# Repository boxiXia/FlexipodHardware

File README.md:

# FlexipodHardware

## 3D rendering and dimension of Flexipod

CAD model for the Flexipod

Flexipod stand on sand

## Prerequisite
Software: Inventor and Cura(or some other slice software for 3D printing)     
Filament: [Cheetah flexible filament, Ninjatek](https://ninjatek.com/cheetah/)
          [PolyMax™ PC, Playmaker](https://www.amazon.com/dp/B01KT3K0FW/?coliid=ISKG6U7RH7ZF8&colid=118CNRRRVL2LQ&psc=1&ref_=lv_ov_lig_dp_it)    
Super glue: [Gorilla Super Glue](https://www.amazon.com/Gorilla-Super-Brush-Nozzle-Applicator/dp/B01LYO4R4I/ref=sr_1_4?crid=1XCD6SS1SOGKY&dchild=1&keywords=super+glue&sprefix=super%2Caps%2C170&sr=8-4)

## Mechiancl parts

All the printed parts are printed by a FDM 3D printer(Troodon Core-XY printer, VIVEDINO) with a standard 0.4 mm nozzle at 0.2 mm layer height. For soft print, skins are only printed at mating surfaces, since the outer skins of the printed parts will greatly reduce the flexibility.

1. leg: print with 16% infill density(Gyroid pattern) and 80% flow using flexible TPU (Cheetah flexible filament, Ninjatek).

2. leg adaptor: rigid filament (PolyMax™ PC, Playmaker)

3. motor mount outer part: print with 20% infill density(Gyroid pattern) and 90% flow using flexible TPU (Cheetah flexible filament, Ninjatek).

4. [bearing: ](https://www.amazon.com/6806-Ceramic-Cartridge-Bearing-30x42x7mm/dp/B01MU6Z46A/ref=sr_1_3?dchild=1&keywords=6806-2RS&qid=1604034211&sr=8-3)

5. motor mount inner part: print with 20% infill density(Gyroid pattern) and 90% flow using flexible TPU (Cheetah flexible filament, Ninjatek).

6. motor shell: rigid filament (PolyMax™ PC, Playmaker)

7. body cover: print with 20% infill density(Gyroid pattern) and 90% flow using flexible TPU (Cheetah flexible filament, Ninjatek).

8. upper body: print with 20% infill density(Gyroid pattern) and 90% flow using flexible TPU (Cheetah flexible filament, Ninjatek).

9. lower body: print with 20% infill density(Gyroid pattern) and 90% flow using flexible TPU (Cheetah flexible filament, Ninjatek).

## Electrical parts
electrical system of the Flexipod  

1. [Raspberry Pi 4B](https://www.amazon.com/Raspberry-Model-2019-Quad-Bluetooth/dp/B07TC2BK1X/ref=sr_1_5?crid=2TAFP75A787CM&dchild=1&keywords=raspberry+pi+4&sprefix=raspberr%2Caps%2C187&sr=8-5)

2. [5V Voltage Regulator](https://www.pololu.com/product/4091)

3. [5S Battery](https://www.amazon.com/Ovonic-1300mAh-Battery-Professional-Competitions/dp/B07JXZCHWM/ref=sr_1_4?dchild=1&keywords=Ovonic+5S+battery&qid=1598477273&sr=8-4)

4. [CAN Transceivez](https://www.amazon.com/dp/B07V5LGBC8/?coliid=I3FNNXJG3YL6HU&colid=34AXXXH87PSUB&psc=1&ref_=lv_ov_lig_dp_it)

5. [Teensy 4.0](https://www.amazon.com/Teensy-4-0-With-Pins/dp/B08259KDHY/ref=sr_1_3?crid=29SHX3YSS7XUC&dchild=1&keywords=teensy+4.0&sprefix=teensy+%2Caps%2C167&sr=8-3)

6. [IMU](https://www.adafruit.com/product/4517)

7. [Voltage Sensor](https://www.adafruit.com/product/4226)

8. [ESC](https://store.dji.com/product/rm-c620-brushless-dc-motor-speed-controller?set_country=US&gclid=EAIaIQobChMI2s7r6Oi56wIVDsDICh1QPgAQEAYYASABEgI1tvD_BwE)

9. [Motor](https://store.dji.com/product/rm-m3508-p19-brushless-dc-gear-motor?set_country=US&gclid=EAIaIQobChMI_8WYiem56wIVluSzCh2VIABiEAYYASABEgJY_vD_BwE)

10. [Custom PCB](https://github.com/boxiXia/FlexipodHardware/tree/master/mechanical_model/PCB/Gerber%20%26%20drill)

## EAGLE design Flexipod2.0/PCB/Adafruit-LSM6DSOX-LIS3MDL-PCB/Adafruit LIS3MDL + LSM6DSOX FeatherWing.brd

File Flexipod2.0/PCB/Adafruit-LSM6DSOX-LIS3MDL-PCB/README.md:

## Adafruit LSM6DSOX + LIS3MDL Precision 9-DoF IMU PCBs

<a href="http://www.adafruit.com/products/4517"><br/>
<a href="http://www.adafruit.com/products/4565"><br/>
Click here to purchase one from the Adafruit shop</a>

PCB files for the Adafruit LSM6DSOX + LIS3MDL Precision 9-DoF IMU breakout and FeatherWing.

Format is EagleCAD schematic and board layout
* https://www.adafruit.com/product/4517

### Description

Add high quality motion, direction and orientation sensing to your Arduino project with this all-in-one 9 Degree of Freedom (9-DoF) sensor with sensors from ST. This little breakout contains two chips that sit side-by-side to provide 9 degrees of full-motion data.

The board includes an LSM6DSOX, a 6-DoF IMU accelerometer + gyro. The 3-axis accelerometer can tell you which direction is down towards the Earth (by measuring gravity) or how fast the board is accelerating in 3D space. The 3-axis gyroscope can measure spin and twist. This new sensor from ST has very low gyro zero rate and noise, compared to the MPU6050 or even LSM6DS33 so it's excellent for orientation fusion usage: you'll get less drift and faster responses.

The LSM6DSOX has flexible data rates and ranges. For the accelerometer: ±2/±4/±8/±16 g at 1.6 Hz to 6.7KHz update rate. For the gyroscope: ±125/±250/±500/±1000/±2000 dps at 12.5 Hz to 6.7 KHz. There's also some nice extras, such as built in tap detection, activity detection, pedometer/step counter and a programmable finite state machine / machine learning core that can perform some basic gesture recognition.

It also includes a LIS3MDL 3-axis magnetometer that can sense where the strongest magnetic force is coming from, generally used to detect magnetic north. The three triple-axis sensors add up to 9 degrees of freedom, by combining this data you can orient the board. Check out our guide on how to do that!

To make getting started fast and easy, we placed the sensors on a compact breakout board with voltage regulation and level-shifted inputs. That way you can use them with 3V or 5V power/logic devices without worry. To make usage simple, we expose only the I2C interface and some interrupt pins from each chip. The breakout comes fully assembled and tested, with some extra header so you can use it on a breadboard. Four mounting holes make for a secure connection.

Additionally, since it speaks I2C you can easily connect it up with two wires (plus power and ground!).  We've even included SparkFun qwiic compatible STEMMA QT connectors for the I2C bus so you don't even need to solder! Just wire up to your favorite micro like the STM32F405 Feather with a plug-and-play cable to get 9 DoF data ASAP. You can change the I2C addresses on the back using the solder jumpers, to have two of these sensor boards on one bus.

We also wrote libraries to help you get these sensors integrated with your Arduino/C++. This library covers the accel/gyro and this library is for the magnetometer. For advanced Arduino usage, ST has their own fully-featured library that includes extras such as FIFO management and tap detection for the LSM6DSOX and also for the LIS3MDL magnetometer.

### License

Adafruit invests time and resources providing this open source design, please support Adafruit and open-source hardware by purchasing products from [Adafruit](https://www.adafruit.com)!

Designed by Limor Fried/Ladyada for Adafruit Industries.

Creative Commons Attribution/Share-Alike, all text above must be included in any redistribution.
See license.txt for additional details.

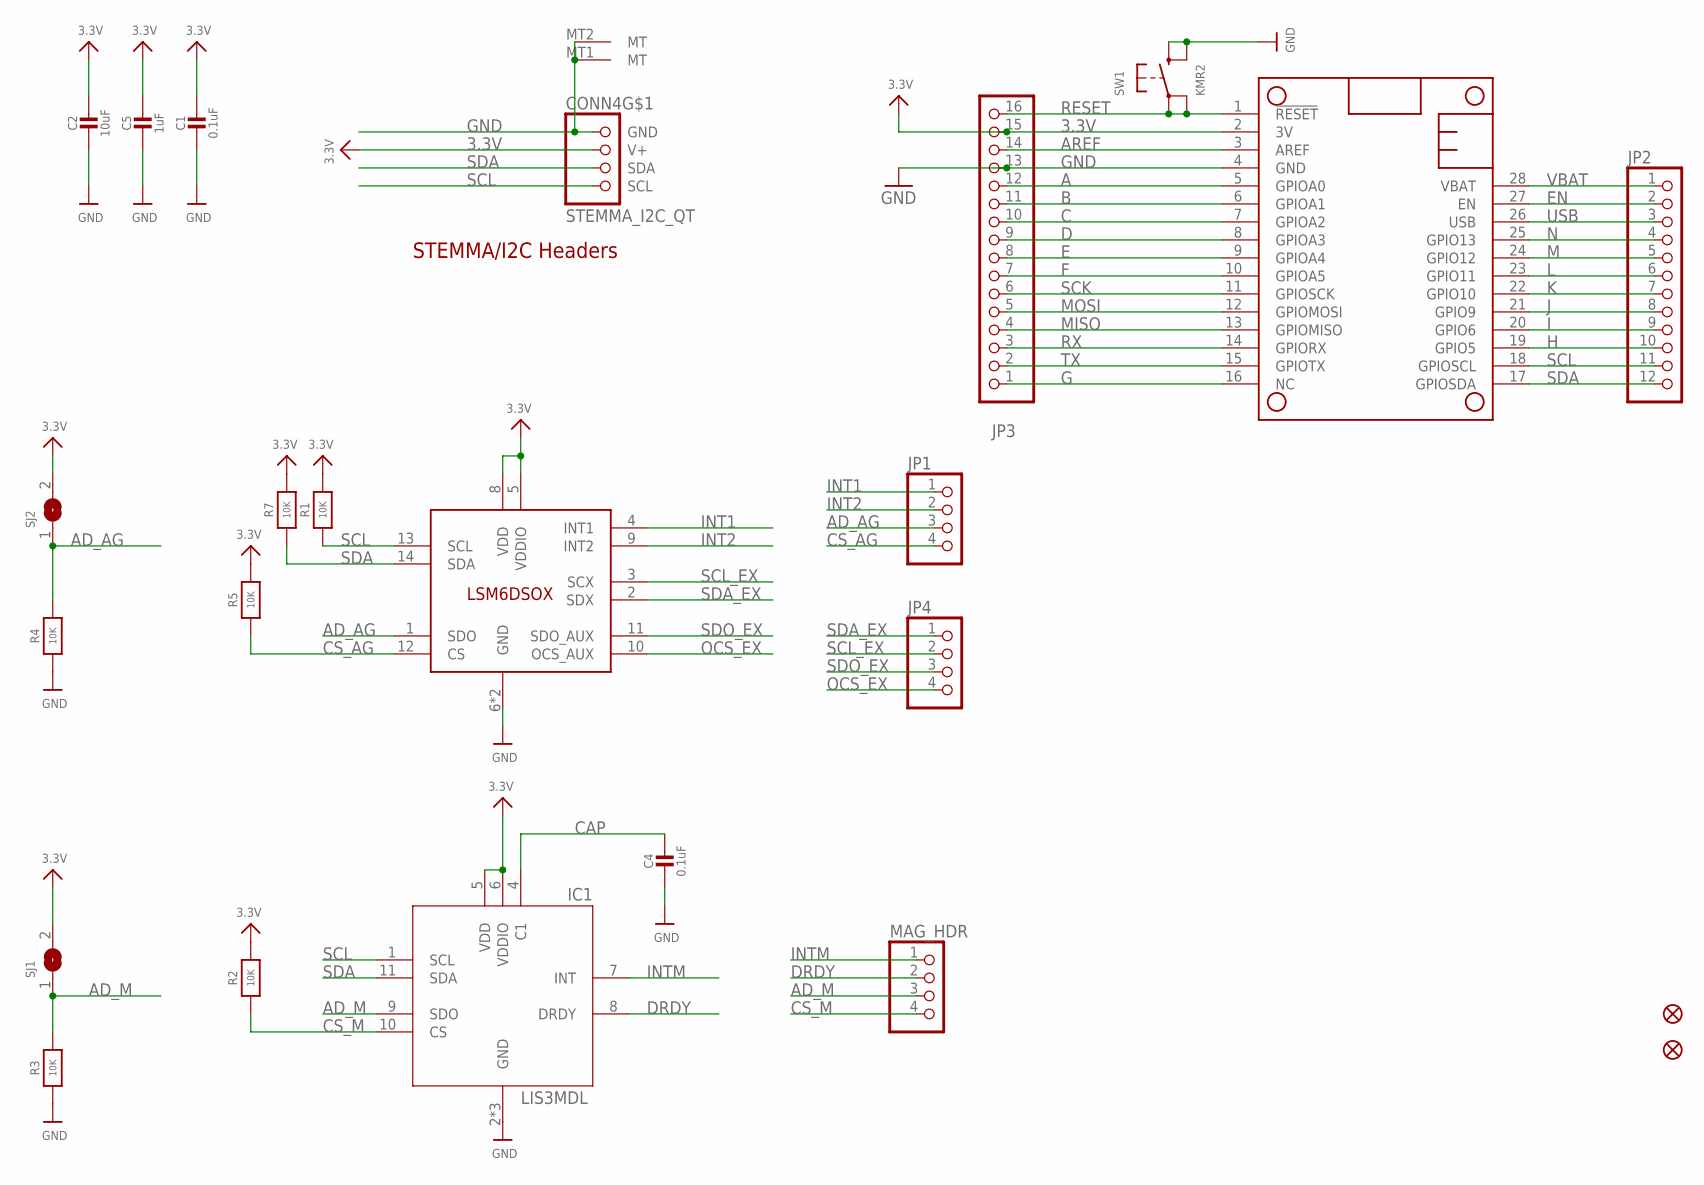
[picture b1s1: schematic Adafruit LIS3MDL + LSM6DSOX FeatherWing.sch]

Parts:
C1, C4: 0.1uF; 0603-NO
C2: 10uF; 0805-NO
C5: 1uF; 0603-NO
CONN4: STEMMA_I2C_QT; JST_SH4
FID1, FID2: FIDUCIAL_1MM
IC1: LIS3MDL; LGA12_2X2MM
JP1, JP4: HEADER-1X4ROUND; 1X04_ROUND
JP2: HEADER-1X12; 1X12_ROUND
JP3: HEADER-1X16ROUND; 1X16_ROUND
MAG_HDR: HEADER-1X4ROUND; 1X04_ROUND
MS1: FEATHERWING
R1, R2, R3, R4, R5, R7: 10K; 0603-NO
SJ1, SJ2: SOLDERJUMPER; SOLDERJUMPER_ARROW_NOPASTE
SW1: KMR2; BTN_KMR2_4.6X2.8
U$35: LSM6DSOX; LGA-14L

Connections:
3.3V: C1.1, C2.1, C5.1, CONN4.2 (V+), IC1.5 (VDD), IC1.6 (VDDIO), JP3.15, MS1.2 (3V), R1.2, R2.2, R5.2, R7.2, SJ1.2, SJ2.2, U$35.5 (VDDIO), U$35.8 (VDD)
A: JP3.12, MS1.5 (GPIOA0)
AD_AG: JP1.3, R4.2, SJ2.1, U$35.1 (SDO)
AD_M: IC1.9 (SDO), MAG_HDR.3, R3.2, SJ1.1
AREF: JP3.14, MS1.3 (AREF)
B: JP3.11, MS1.6 (GPIOA1)
C: JP3.10, MS1.7 (GPIOA2)
CAP: C4.1, IC1.4 (C1)
CS_AG: JP1.4, R5.1, U$35.12 (CS)
CS_M: IC1.10 (CS), MAG_HDR.4, R2.1
D: JP3.9, MS1.8 (GPIOA3)
DRDY: IC1.8 (DRDY), MAG_HDR.2
E: JP3.8, MS1.9 (GPIOA4)
EN: JP2.2, MS1.27 (EN)
F: JP3.7, MS1.10 (GPIOA5)
G: JP3.1, MS1.16 (NC)
GND: C1.2, C2.2, C4.2, C5.2, CONN4.1 (GND), CONN4.MT1 (MT), CONN4.MT2 (MT), IC1.2 (GND), IC1.3 (GND), IC1.12 (GND), JP3.13, MS1.4 (GND), R3.1, R4.1, SW1.B (S), SW1.B' (S1), U$35.6 (GND), U$35.7 (GND)
H: JP2.10, MS1.19 (GPIO5)
I: JP2.9, MS1.20 (GPIO6)
INT1: JP1.1, U$35.4 (INT1)
INT2: JP1.2, U$35.9 (INT2)
INTM: IC1.7 (INT), MAG_HDR.1
J: JP2.8, MS1.21 (GPIO9)
K: JP2.7, MS1.22 (GPIO10)
L: JP2.6, MS1.23 (GPIO11)
M: JP2.5, MS1.24 (GPIO12)
MISO: JP3.4, MS1.13 (GPIOMISO)
MOSI: JP3.5, MS1.12 (GPIOMOSI)
N: JP2.4, MS1.25 (GPIO13)
OCS_EX: JP4.4, U$35.10 (OCS_AUX)
RESET: JP3.16, MS1.1 (!RESET), SW1.A, SW1.A' (P1)
RX: JP3.3, MS1.14 (GPIORX)
SCK: JP3.6, MS1.11 (GPIOSCK)
SCL: CONN4.4 (SCL), IC1.1 (SCL), JP2.11, MS1.18 (GPIOSCL), R1.1, U$35.13 (SCL)
SCL_EX: JP4.2, U$35.3 (SCX)
SDA: CONN4.3 (SDA), IC1.11 (SDA), JP2.12, MS1.17 (GPIOSDA), R7.1, U$35.14 (SDA)
SDA_EX: JP4.1, U$35.2 (SDX)
SDO_EX: JP4.3, U$35.11 (SDO_AUX)
TX: JP3.2, MS1.15 (GPIOTX)
USB: JP2.3, MS1.26 (USB)
VBAT: JP2.1, MS1.28 (VBAT)

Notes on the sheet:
STEMMA/I2C Headers

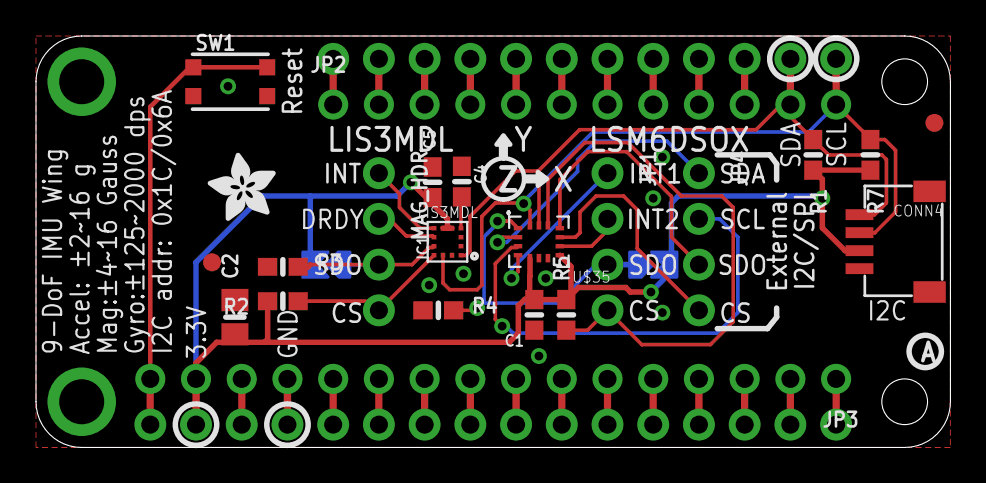
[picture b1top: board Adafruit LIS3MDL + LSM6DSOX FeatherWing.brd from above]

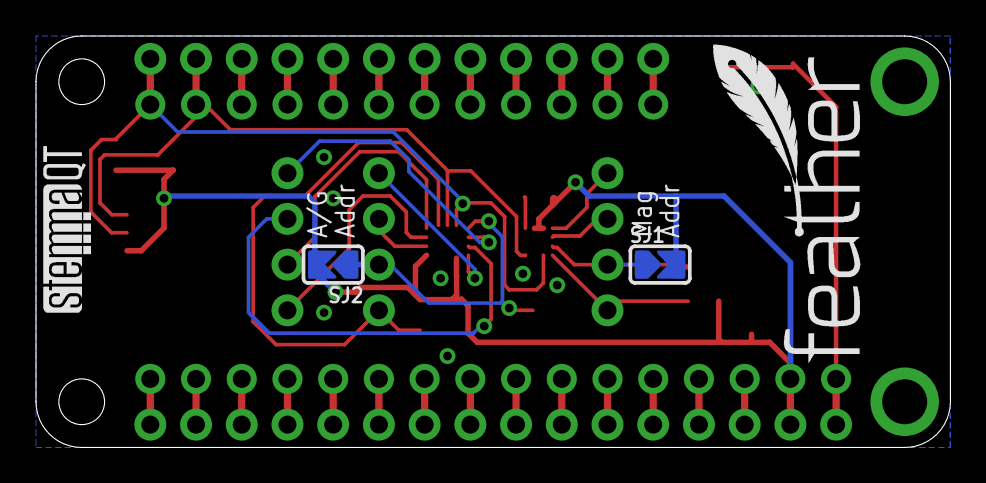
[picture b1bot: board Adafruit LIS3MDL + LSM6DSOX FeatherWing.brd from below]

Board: 2 copper layers, 50.8 x 22.9 mm, 28 parts (4 on the bottom side), 41 nets.

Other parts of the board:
U$13: FEATHERLOGO_MED
U$31: STEMMAQT
U$50: ADAFRUIT_3.5MM
U$51: PCBFEAT-REV-040

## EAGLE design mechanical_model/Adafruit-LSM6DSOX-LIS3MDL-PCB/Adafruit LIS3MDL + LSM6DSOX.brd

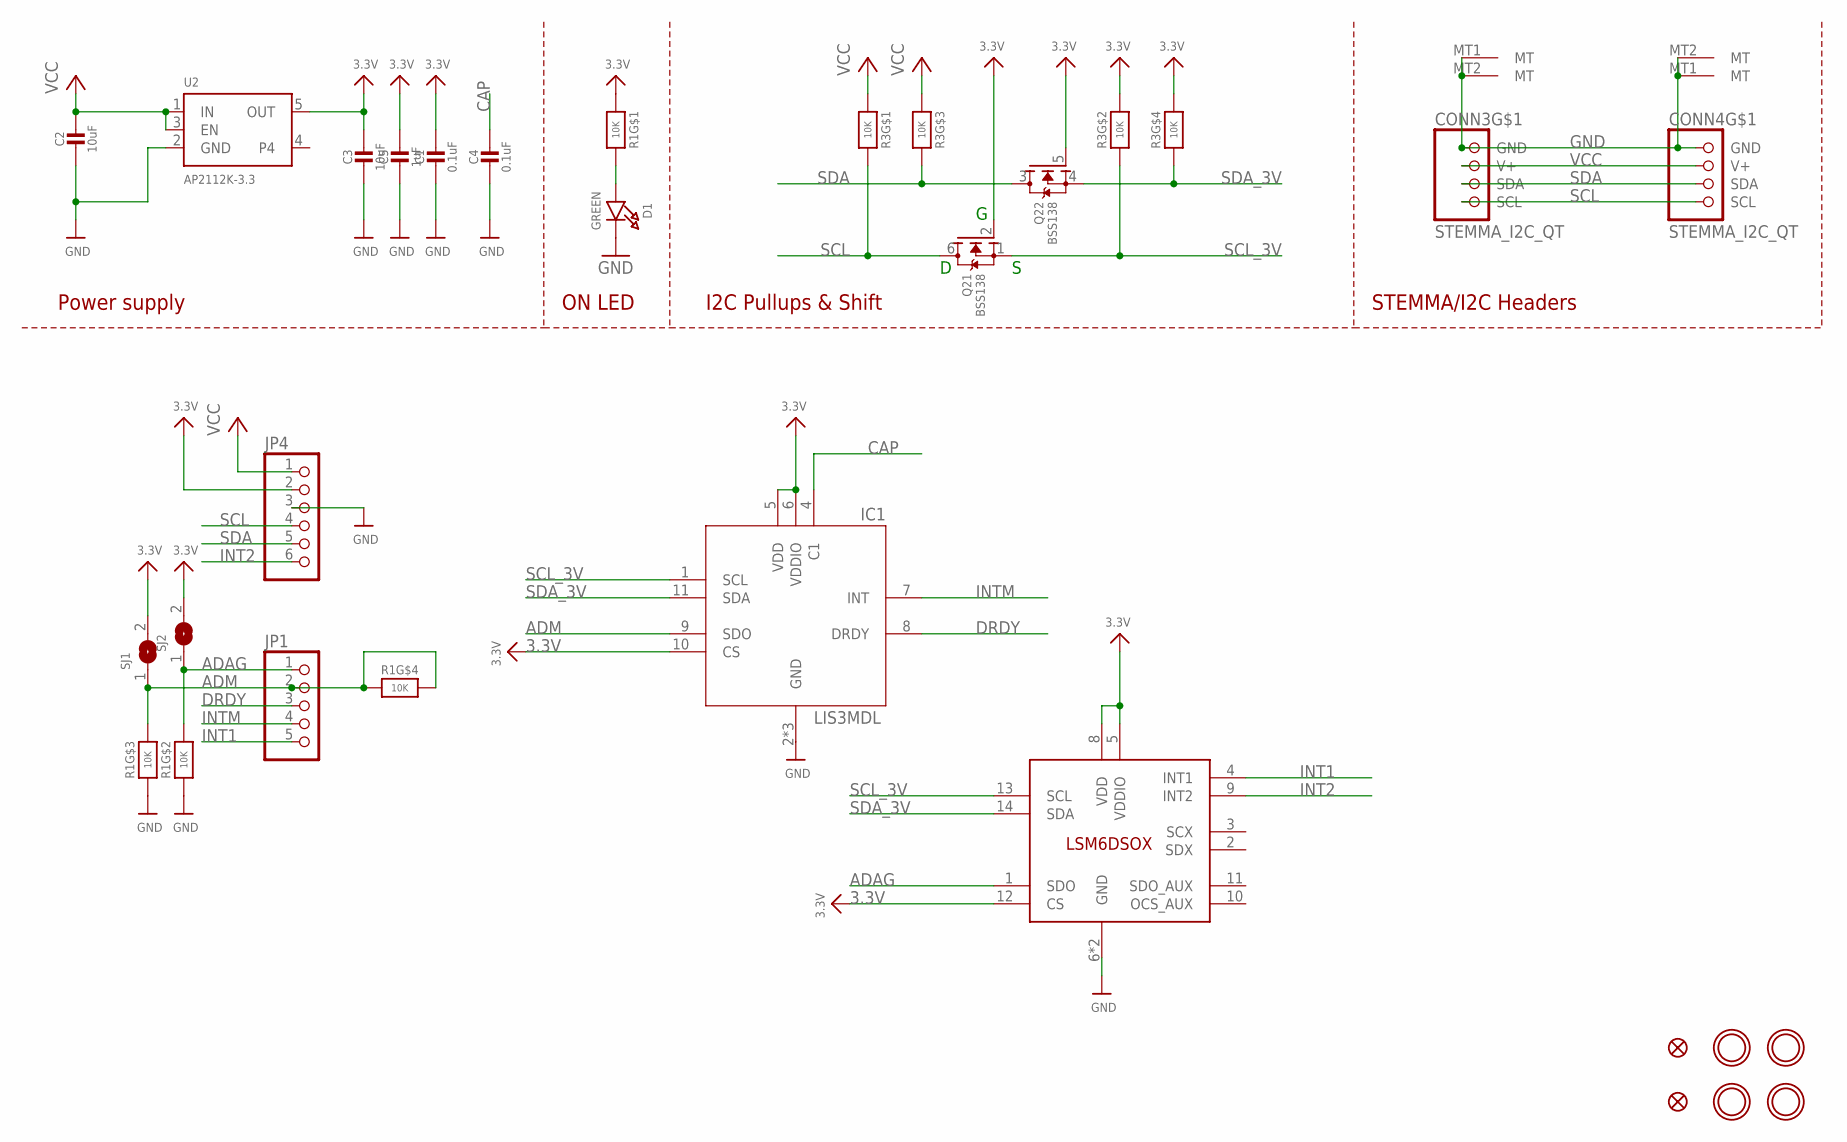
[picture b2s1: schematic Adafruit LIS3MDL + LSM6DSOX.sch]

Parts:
C1, C4: 0.1uF; 0603-NO
C2, C3: 10uF; 0805-NO
C5: 1uF; 0603-NO
CONN3, CONN4: STEMMA_I2C_QT; JST_SH4
D1: GREEN; CHIPLED_0603_NOOUTLINE
FID3, FID4: FIDUCIAL_1MM
IC1: LIS3MDL; LGA12_2X2MM
JP1: HEADER-1X570MIL; 1X05_ROUND_70
JP4: HEADER-1X670MIL; 1X06_ROUND_70
Q2: BSS138; SOT363
R1, R3: 10K; RESPACK_4X0603
SJ1, SJ2: SOLDERJUMPER; SOLDERJUMPER_ARROW_NOPASTE
U2: AP2112K-3.3; SOT23-5
U$1, U$17, U$19, U$21: MOUNTINGHOLE2.5; MOUNTINGHOLE_2.5_PLATED
U$35: LSM6DSOX; LGA-14L

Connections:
3.3V: C1.1, C3.1, C5.1, IC1.5 (VDD), IC1.6 (VDDIO), IC1.10 (CS), JP4.2, Q2.2 (G), Q2.5 (G), R1.1, R3.2 (1), R3.4 (1), SJ1.2, SJ2.2, U2.5 (OUT), U$35.5 (VDDIO), U$35.8 (VDD), U$35.12 (CS)
ADAG: JP1.1, R1.7 (2), SJ2.1, U$35.1 (SDO)
ADM: IC1.9 (SDO), JP1.2, R1.4 (1), R1.5 (2), R1.6 (2), SJ1.1
CAP: C4.1, IC1.4 (C1)
DRDY: IC1.8 (DRDY), JP1.3
GND: C1.2, C2.2, C3.2, C4.2, C5.2, CONN3.1 (GND), CONN3.MT1 (MT), CONN3.MT2 (MT), CONN4.1 (GND), CONN4.MT1 (MT), CONN4.MT2 (MT), D1.C, IC1.2 (GND), IC1.3 (GND), IC1.12 (GND), JP4.3, R1.2 (1), R1.3 (1), U2.2 (GND), U$35.6 (GND), U$35.7 (GND)
INT1: JP1.5, U$35.4 (INT1)
INT2: JP4.6, U$35.9 (INT2)
INTM: IC1.7 (INT), JP1.4
unnamed: D1.A, R1.8 (2)
SCL: CONN3.4 (SCL), CONN4.4 (SCL), JP4.4, Q2.6 (D), R3.8 (2)
SCL_3V: IC1.1 (SCL), Q2.1 (S), R3.7 (2), U$35.13 (SCL)
SDA: CONN3.3 (SDA), CONN4.3 (SDA), JP4.5, Q2.3 (D), R3.6 (2)
SDA_3V: IC1.11 (SDA), Q2.4 (S), R3.5 (2), U$35.14 (SDA)
VCC: C2.1, CONN3.2 (V+), CONN4.2 (V+), JP4.1, R3.1, R3.3 (1), U2.1 (IN), U2.3 (EN)

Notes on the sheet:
I2C Pullups & Shift
STEMMA/I2C Headers
ON LED
Power supply

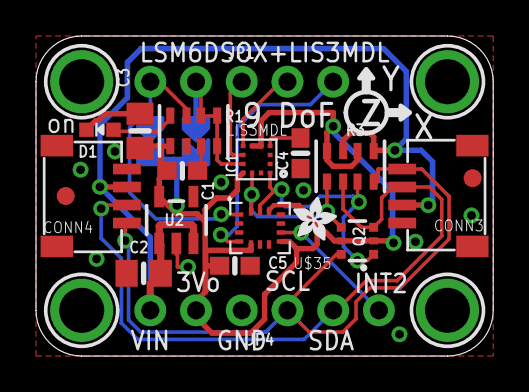
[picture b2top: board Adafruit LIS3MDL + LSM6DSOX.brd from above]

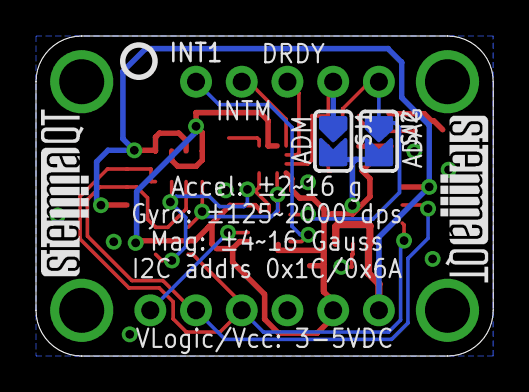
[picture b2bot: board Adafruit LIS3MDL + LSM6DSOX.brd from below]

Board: 2 copper layers, 25.4 x 17.8 mm, 28 parts (5 on the bottom side), 15 nets.

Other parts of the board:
U$20: ADAFRUIT_2.5MM
U$25: PCBFEAT-REV-040
U$30, U$31: STEMMAQT

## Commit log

2020-09-30 bigger and longer version with camera
2020-10-03 checkpoint
2020-10-03 clean up
2020-10-03 updated main body
2020-10-03 Main body modified 10/3/2020
2020-10-04 Change skin for mount_front_in & out part
2020-10-05 body modified 10_5_2020
2020-10-05 Auto stash before merge of "master" and "origin/master"
2020-10-06 edit model for printing 2020 10 6
2020-10-07 changed leg geometry
2020-10-16 add test block
2020-10-16 lesser skin version
2020-10-16 update lesser skin version
2020-10-17 motor front in
2020-10-17 motor front out
2020-10-21 stronger coupler
2020-10-29 images and part of README
2020-10-30 images for README
2020-10-30 images
2020-10-30 update image for README
2020-11-06 picture update
2020-11-07 Gerber and drill file
2021-01-03 new_robot
2021-01-04 new version of robot
2021-01-04 robot_update
2021-01-05 Cadquery module
2021-01-06 new robot
2021-01-10 new robot body
2021-01-17 2021-1-16
2021-01-29 2021-1-28
2021-01-29 remove oldversion
2021-01-29 v8.0
2021-01-29 add schematics
2021-02-14 2021_2_13 new robot and animation
2021-02-17 2021_2_17 quadrupedal animation
2021-03-02 2021_3_2
2021-03-03 Revert "2021_3_2"
    This reverts commit 6a2f6ec22f45fea52d3db1f25e79a154aa203195.
2021-03-03 2021_3_3
2021-03-03 new design
2021-03-03 edit the motor protector
2021-03-04 edit front hip

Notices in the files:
parts and their libraries:
microbuilder: This work is placed in the public domain, and may be freely used for commercial and non-commercial work with the following conditions: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
